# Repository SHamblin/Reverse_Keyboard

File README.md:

# Reverse_Keyboard
This is a diy mechanical keyboard with the numberpad on the left.

The primay goal of this project is to design a cherry mx compatable keyboard with the numberpad on the left.
Seconday goals include integrating a encoder for volume control a designing a stylish case
Stretch goals include intetgrating a fingerprint reader and a USB hub.

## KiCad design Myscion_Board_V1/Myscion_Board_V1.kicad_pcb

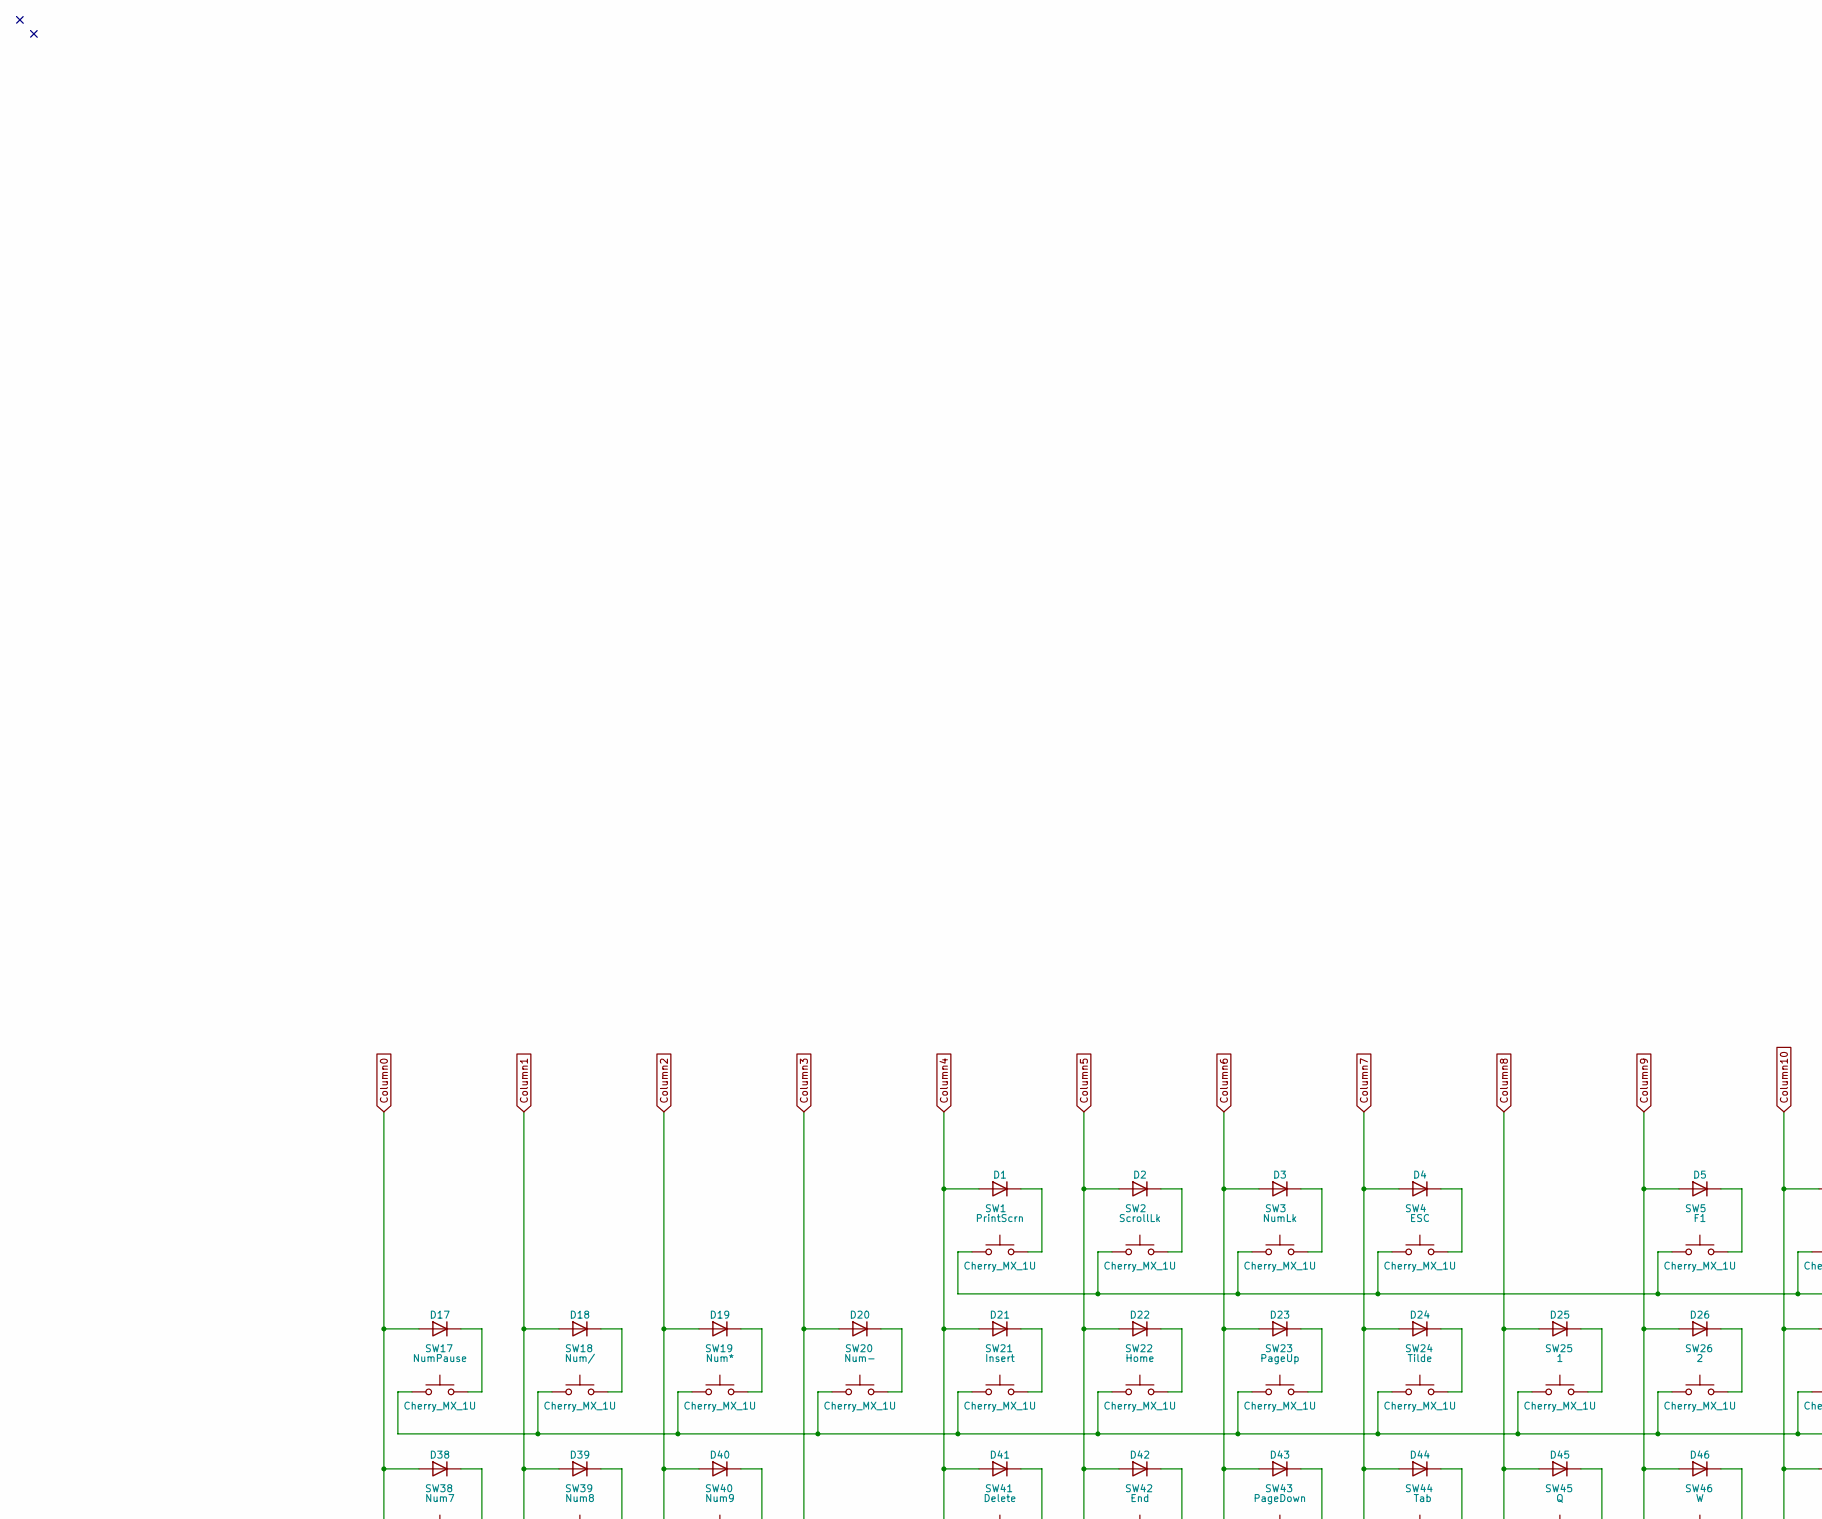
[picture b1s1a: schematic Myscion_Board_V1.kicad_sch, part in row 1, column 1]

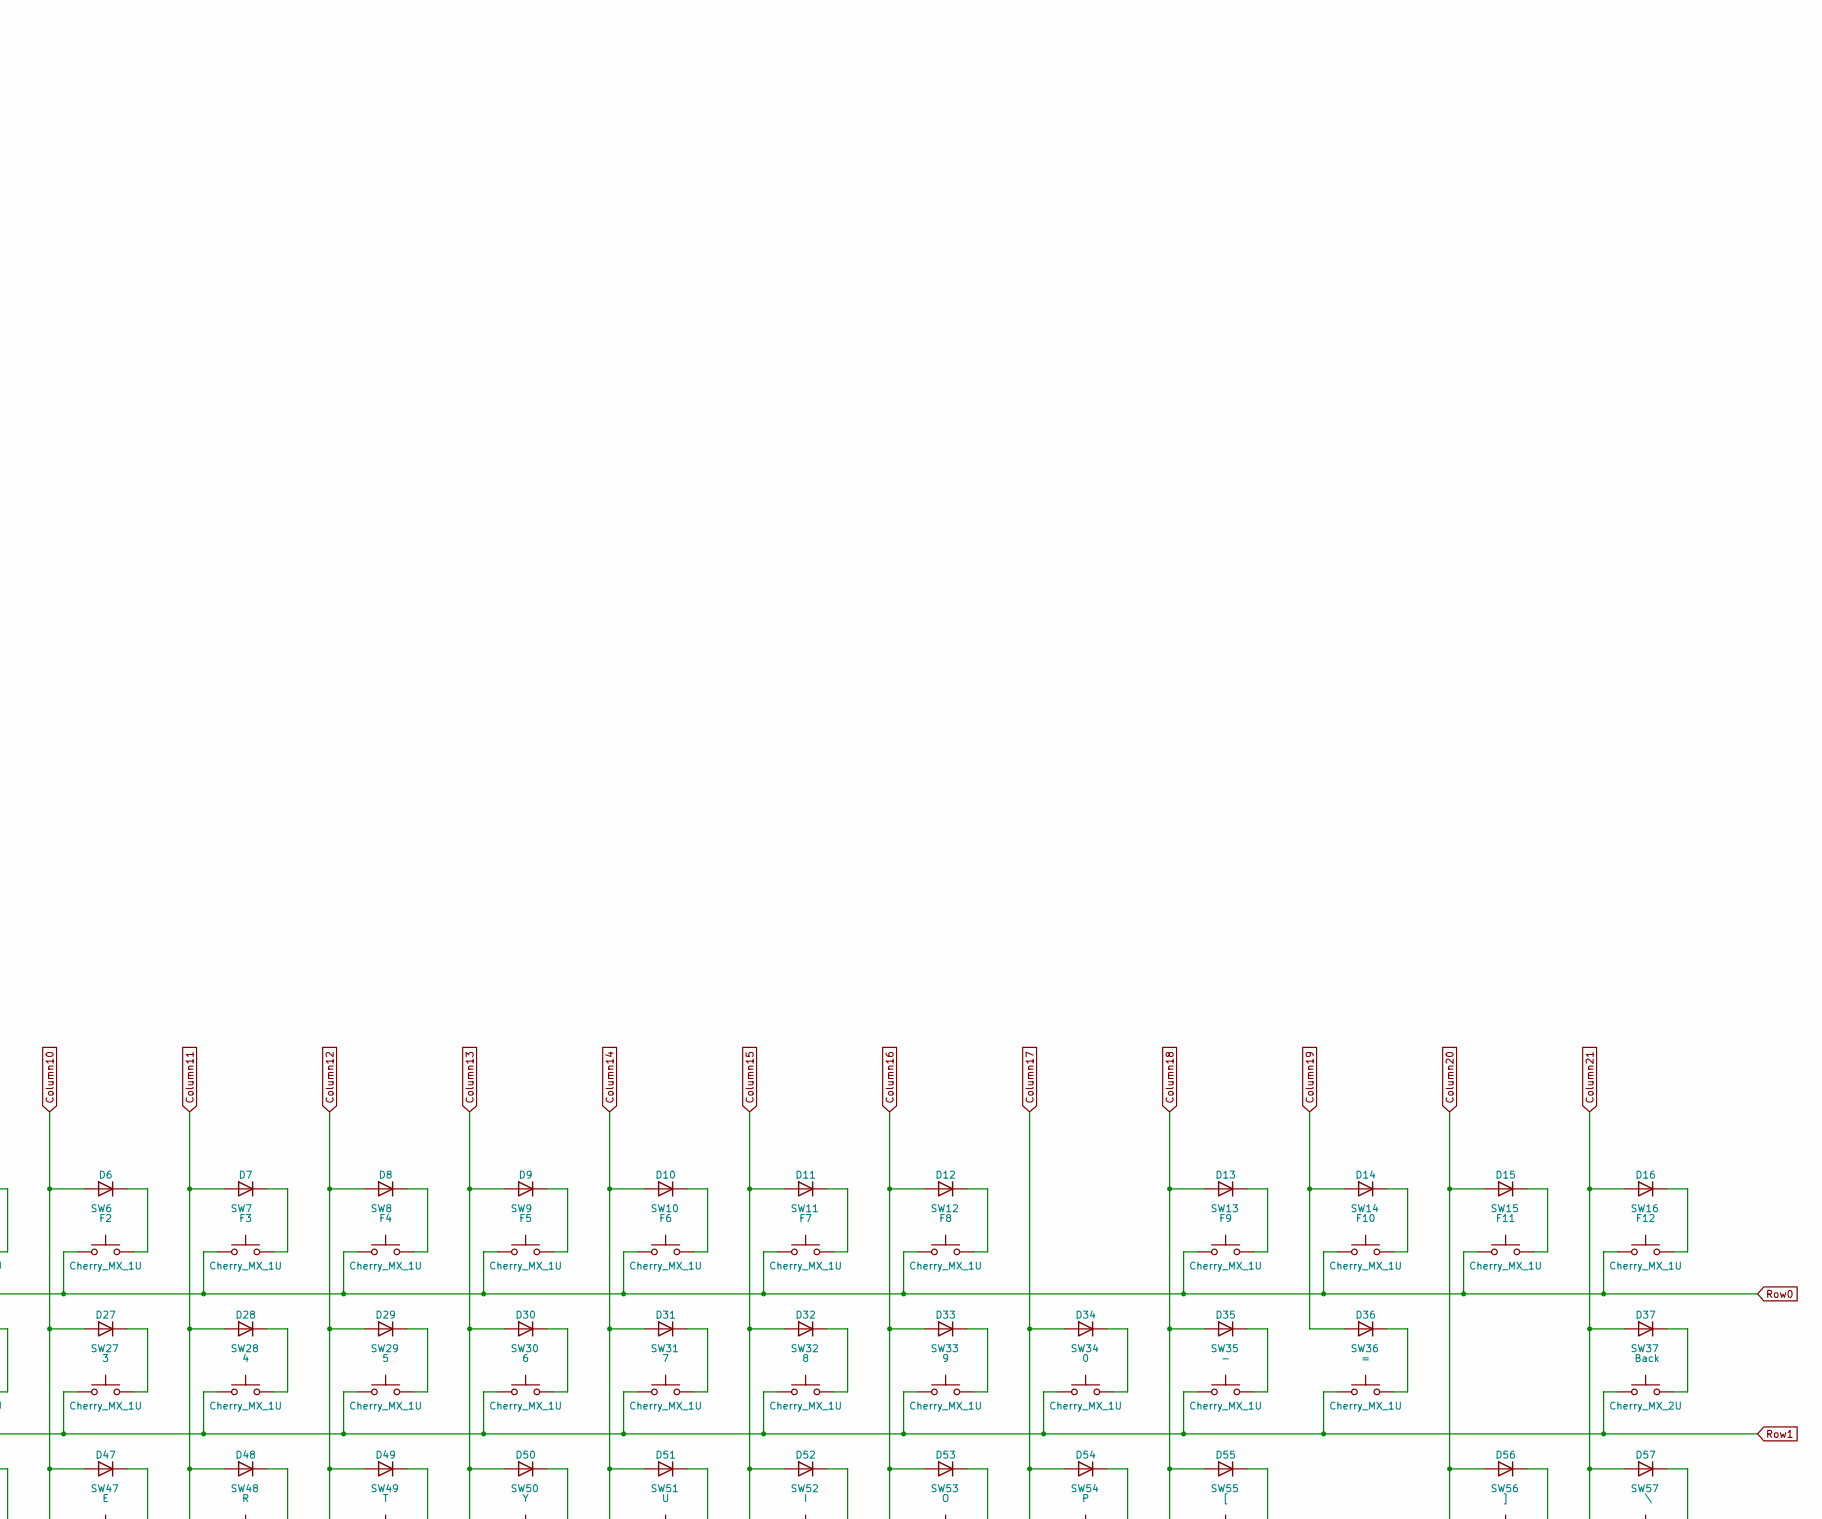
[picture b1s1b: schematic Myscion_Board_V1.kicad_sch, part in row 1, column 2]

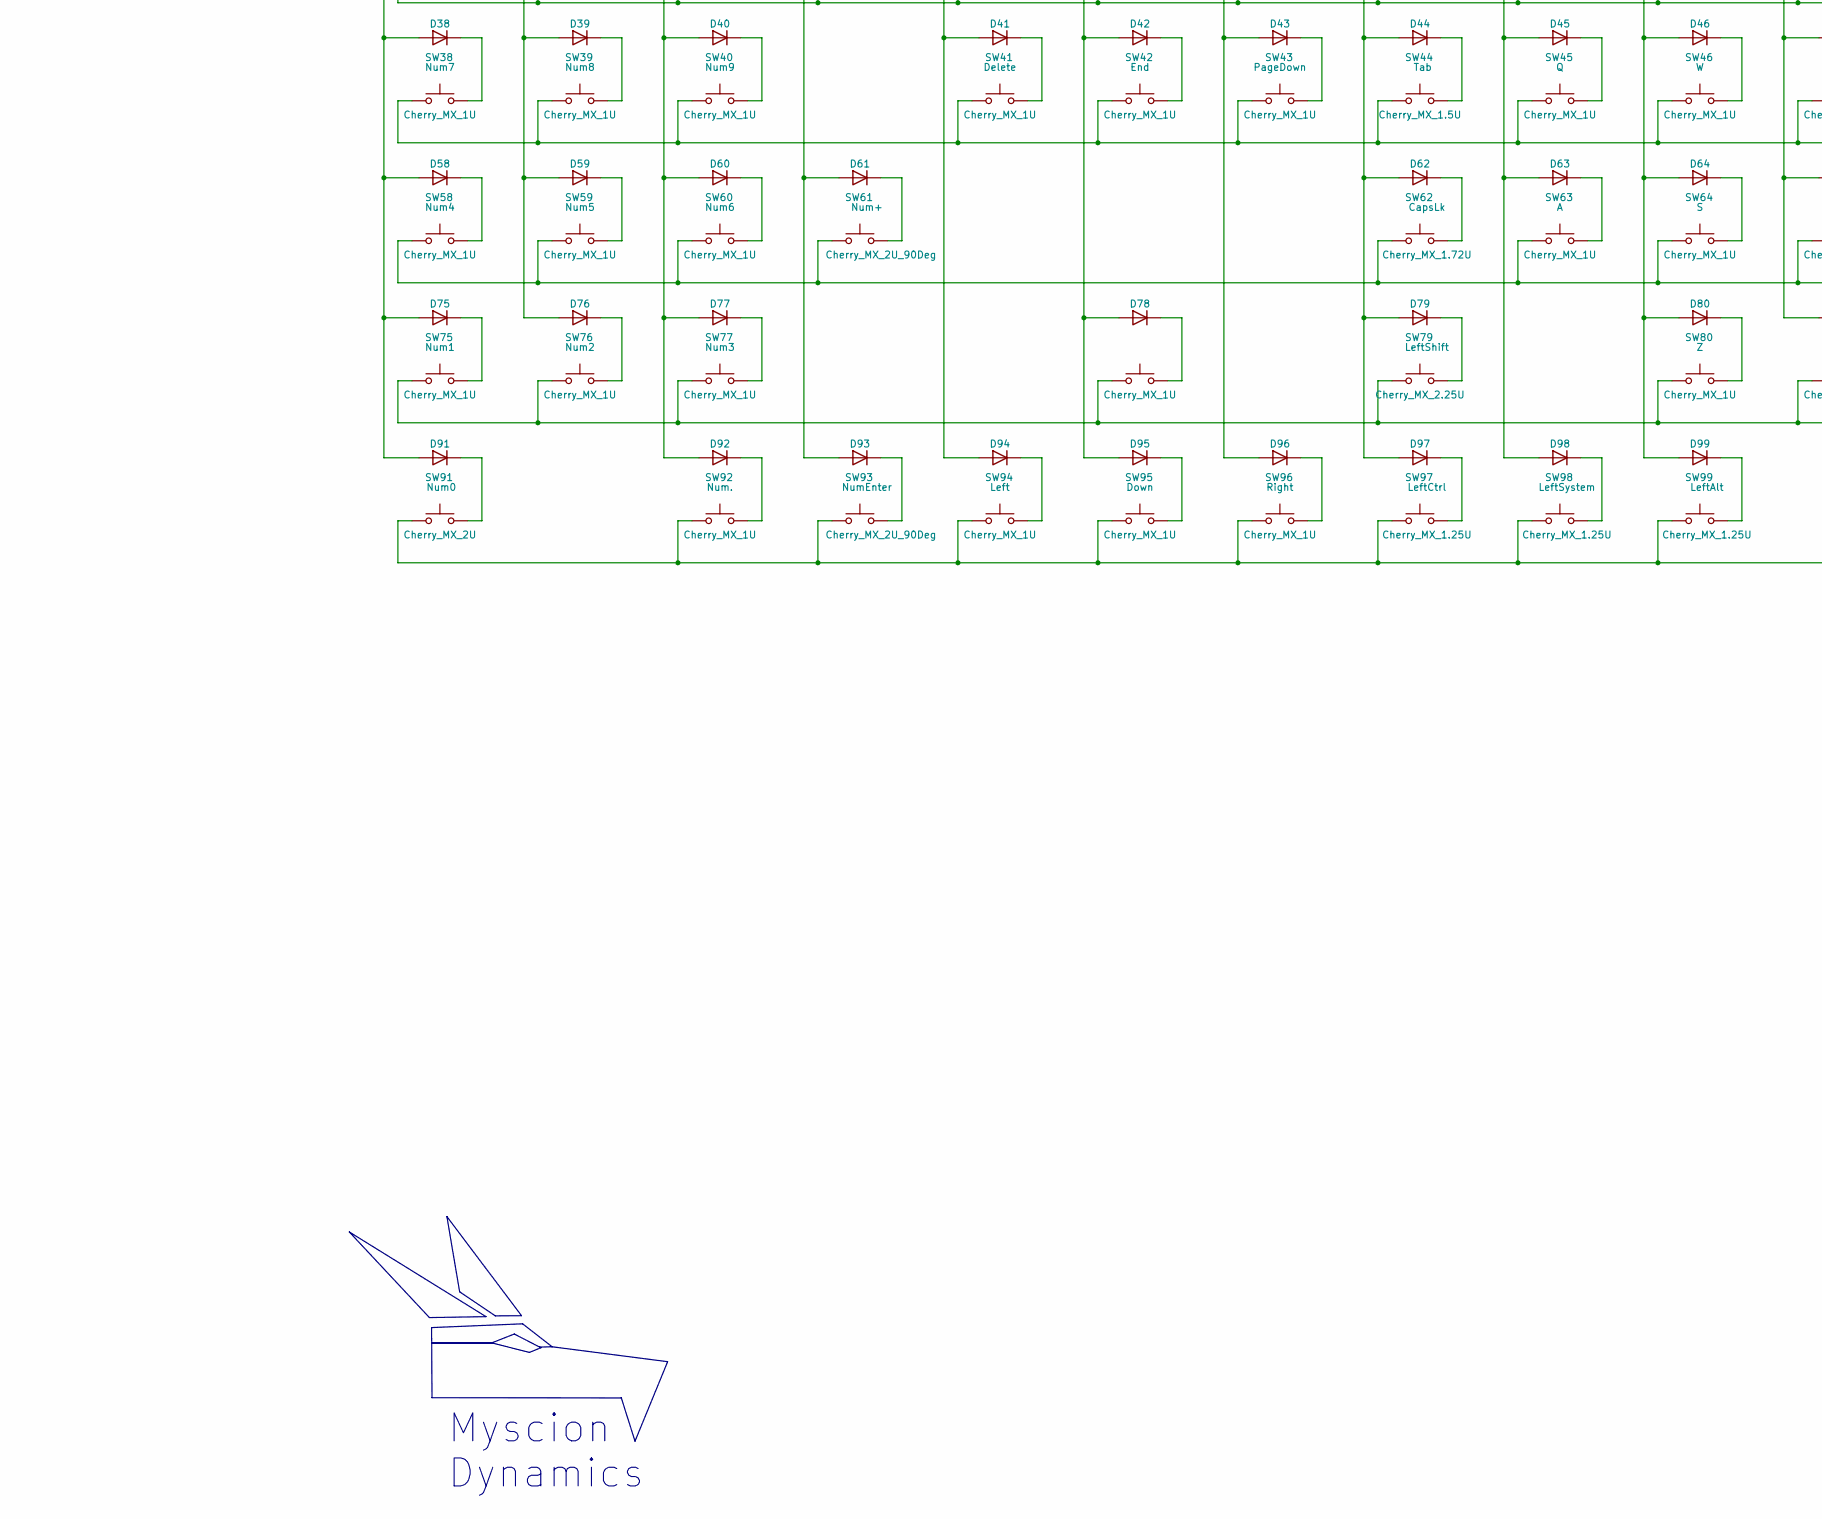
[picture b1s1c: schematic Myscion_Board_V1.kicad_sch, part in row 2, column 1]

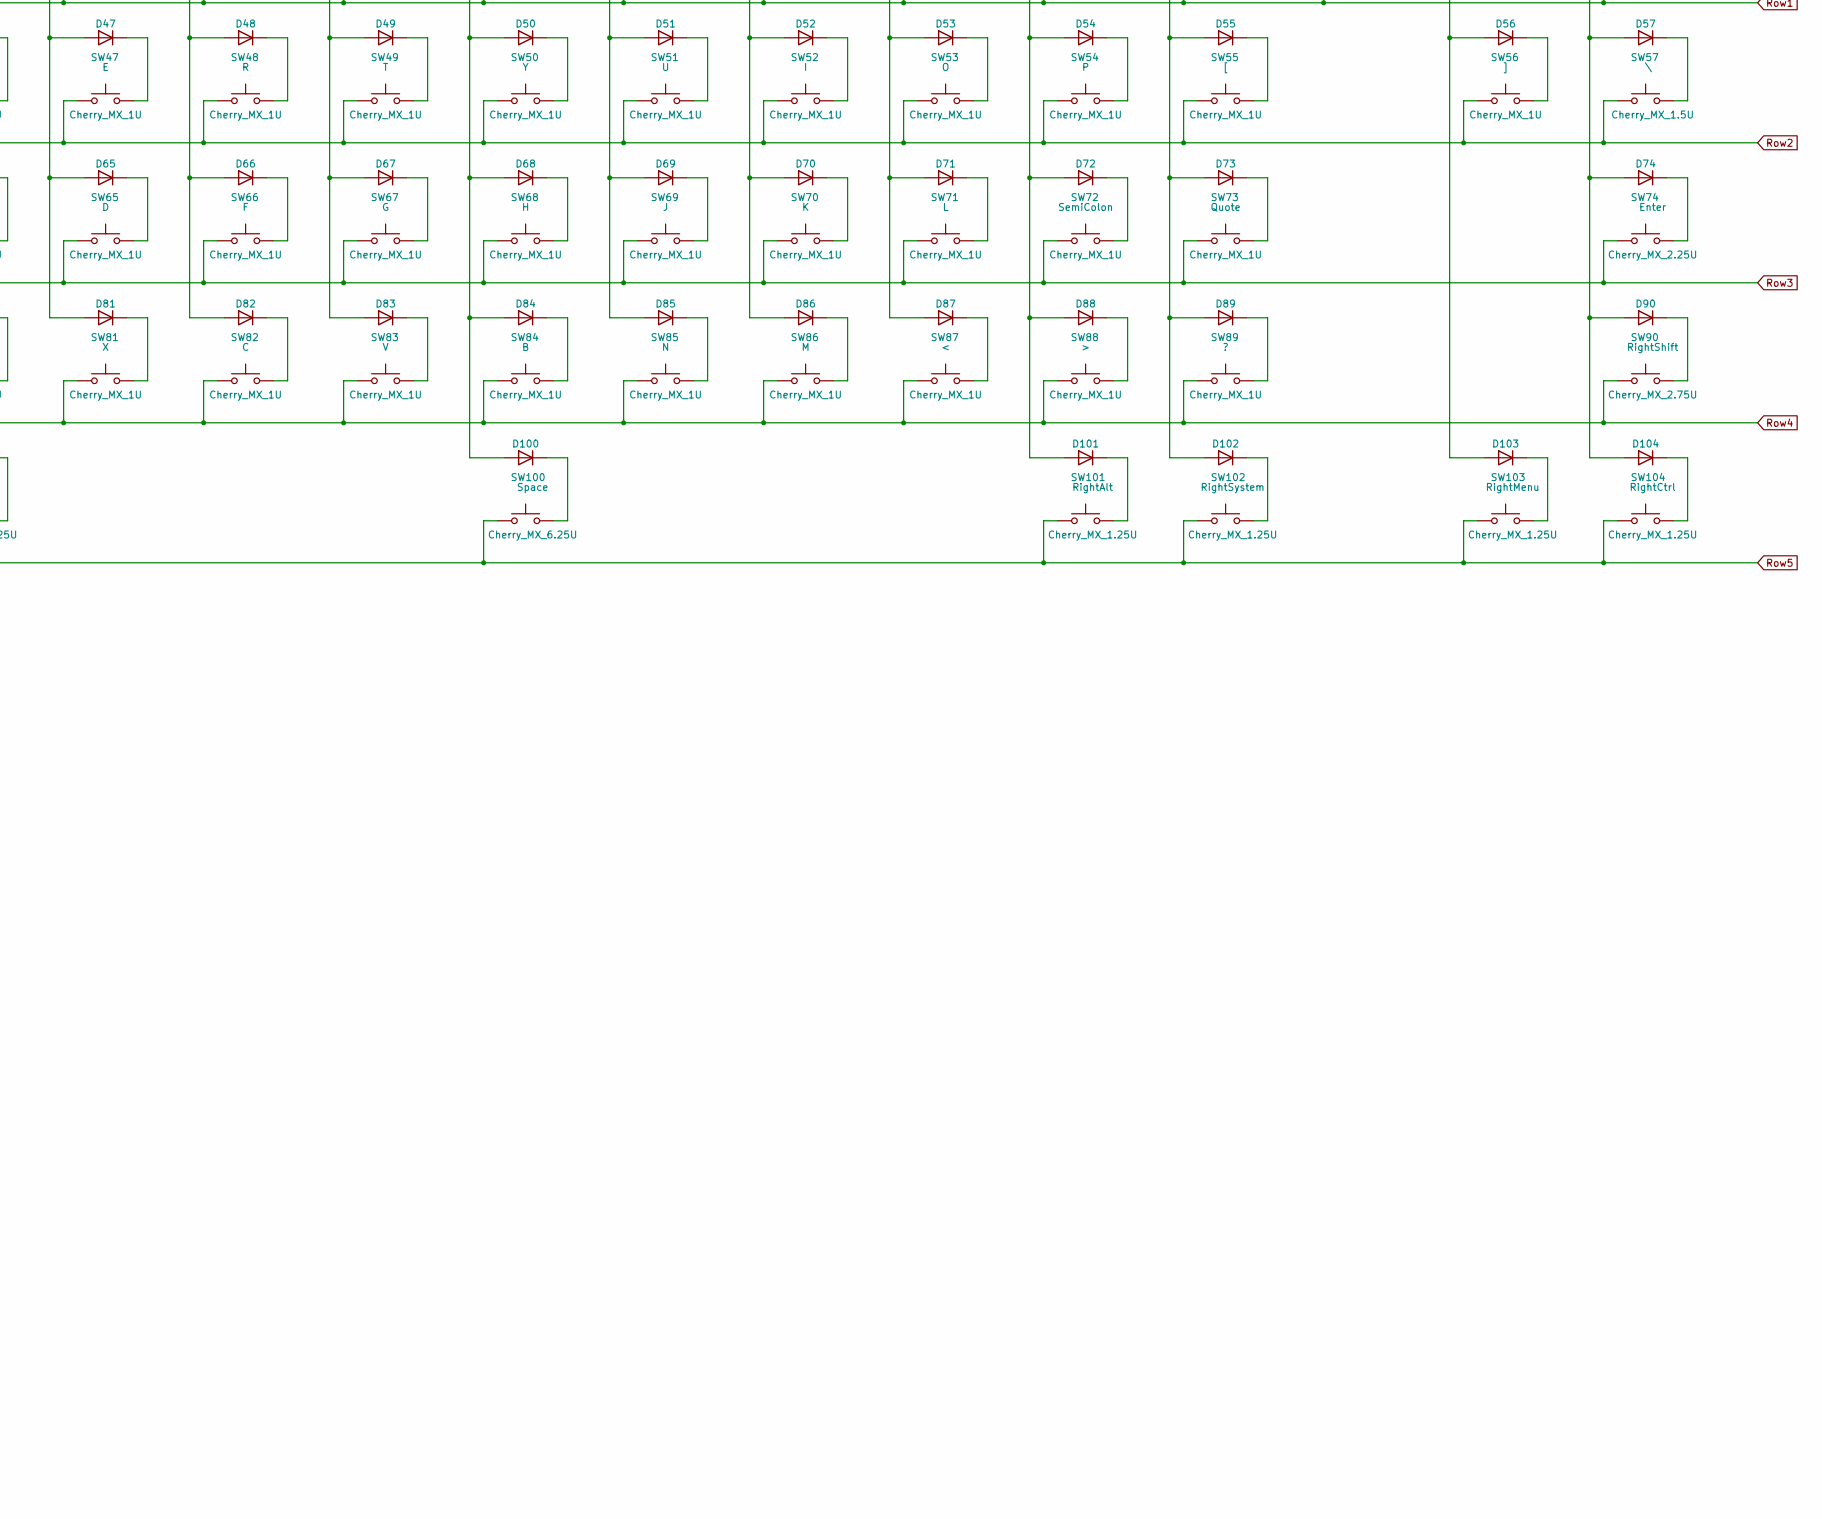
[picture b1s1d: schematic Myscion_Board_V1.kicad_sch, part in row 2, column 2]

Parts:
D1, D2, D3, D4, D5, D6, D7, D8, D9, D10, D11, D12, D13, D14, D15, D16, D17, D18, D19, D20, D21, D22, D23, D24, D25, D26, D27, D28, D29, D30, D31, D32, D33, D34, D35, D36, D37, D38, D39, D40, D41, D42, D43, D44, D45, D46, D47, D48, D49, D50, D51, D52, D53, D54, D55, D56, D57, D58, D59, D60, D61, D62, D63, D64, D65, D66, D67, D68, D69, D70, D71, D72, D73, D74, D75, D76, D77, D78, D79, D80, D81, D82, D83, D84, D85, D86, D87, D88, D89, D90, D91, D92, D93, D94, D95, D96, D97, D98, D99, D100, D101, D102, D103, D104: 75V; D_SOD-123; MPN 1N4148W
SW1: PrintScrn; SW_Cherry_MX_PCB_1.00u; MPN Unkown
SW2: ScrollLk; SW_Cherry_MX_PCB_1.00u; MPN Unkown
SW3: NumLk; SW_Cherry_MX_PCB_1.00u; MPN Unkown
SW4: ESC; SW_Cherry_MX_PCB_1.00u; MPN Unkown
SW5: F1; SW_Cherry_MX_PCB_1.00u; MPN Unkown
SW6: F2; SW_Cherry_MX_PCB_1.00u; MPN Unkown
SW7: F3; SW_Cherry_MX_PCB_1.00u; MPN Unkown
SW8: F4; SW_Cherry_MX_PCB_1.00u; MPN Unkown
SW9: F5; SW_Cherry_MX_PCB_1.00u; MPN Unkown
SW10: F6; SW_Cherry_MX_PCB_1.00u; MPN Unkown
SW11: F7; SW_Cherry_MX_PCB_1.00u; MPN Unkown
SW12: F8; SW_Cherry_MX_PCB_1.00u; MPN Unkown
SW13: F9; SW_Cherry_MX_PCB_1.00u; MPN Unkown
SW14: F10; SW_Cherry_MX_PCB_1.00u; MPN Unkown
SW15: F11; SW_Cherry_MX_PCB_1.00u; MPN Unkown
SW16: F12; SW_Cherry_MX_PCB_1.00u; MPN Unkown
SW17: NumPause; SW_Cherry_MX_PCB_1.00u; MPN Unkown
SW18: Num/; SW_Cherry_MX_PCB_1.00u; MPN Unkown
SW19: Num*; SW_Cherry_MX_PCB_1.00u; MPN Unkown
SW20: Num-; SW_Cherry_MX_PCB_1.00u; MPN Unkown
SW21: Insert; SW_Cherry_MX_PCB_1.00u; MPN Unkown
SW22: Home; SW_Cherry_MX_PCB_1.00u; MPN Unkown
SW23: PageUp; SW_Cherry_MX_PCB_1.00u; MPN Unkown
SW24: Tilde; SW_Cherry_MX_PCB_1.00u; MPN Unkown
SW25: 1; SW_Cherry_MX_PCB_1.00u; MPN Unkown
SW26: 2; SW_Cherry_MX_PCB_1.00u; MPN Unkown
SW27: 3; SW_Cherry_MX_PCB_1.00u; MPN Unkown
SW28: 4; SW_Cherry_MX_PCB_1.00u; MPN Unkown
SW29: 5; SW_Cherry_MX_PCB_1.00u; MPN Unkown
SW30: 6; SW_Cherry_MX_PCB_1.00u; MPN Unkown
SW31: 7; SW_Cherry_MX_PCB_1.00u; MPN Unkown
SW32: 8; SW_Cherry_MX_PCB_1.00u; MPN Unkown
SW33: 9; SW_Cherry_MX_PCB_1.00u; MPN Unkown
SW34: 0; SW_Cherry_MX_PCB_1.00u; MPN Unkown
SW35: -; SW_Cherry_MX_PCB_1.00u; MPN Unkown
SW36: =; SW_Cherry_MX_PCB_1.00u; MPN Unkown
SW37: Back; SW_Cherry_MX_PCB_2.00u; MPN Unkown
SW38: Num7; SW_Cherry_MX_PCB_1.00u; MPN Unkown
SW39: Num8; SW_Cherry_MX_PCB_1.00u; MPN Unkown
SW40: Num9; SW_Cherry_MX_PCB_1.00u; MPN Unkown
SW41: Delete; SW_Cherry_MX_PCB_1.00u; MPN Unkown
SW42: End; SW_Cherry_MX_PCB_1.00u; MPN Unkown
SW43: PageDown; SW_Cherry_MX_PCB_1.00u; MPN Unkown
SW44: Tab; SW_Cherry_MX_PCB_1.50u; MPN Unkown
SW45: Q; SW_Cherry_MX_PCB_1.00u; MPN Unkown
SW46: W; SW_Cherry_MX_PCB_1.00u; MPN Unkown
SW47: E; SW_Cherry_MX_PCB_1.00u; MPN Unkown
SW48: R; SW_Cherry_MX_PCB_1.00u; MPN Unkown
SW49: T; SW_Cherry_MX_PCB_1.00u; MPN Unkown
SW50: Y; SW_Cherry_MX_PCB_1.00u; MPN Unkown
SW51: U; SW_Cherry_MX_PCB_1.00u; MPN Unkown
SW52: I; SW_Cherry_MX_PCB_1.00u; MPN Unkown
SW53: O; SW_Cherry_MX_PCB_1.00u; MPN Unkown
SW54: P; SW_Cherry_MX_PCB_1.00u; MPN Unkown
SW55: [; SW_Cherry_MX_PCB_1.00u; MPN Unkown
SW56: ]; SW_Cherry_MX_PCB_1.00u; MPN Unkown
SW57: \; SW_Cherry_MX_PCB_1.50u; MPN Unkown
SW58: Num4; SW_Cherry_MX_PCB_1.00u; MPN Unkown
SW59: Num5; SW_Cherry_MX_PCB_1.00u; MPN Unkown
SW60: Num6; SW_Cherry_MX_PCB_1.00u; MPN Unkown
SW61: Num+; SW_Cherry_MX_PCB_2.00u_90deg; MPN Unkown
SW62: CapsLk; SW_Cherry_MX_PCB_1.75u; MPN Unkown
SW63: A; SW_Cherry_MX_PCB_1.00u; MPN Unkown
SW64: S; SW_Cherry_MX_PCB_1.00u; MPN Unkown
SW65: D; SW_Cherry_MX_PCB_1.00u; MPN Unkown
SW66: F; SW_Cherry_MX_PCB_1.00u; MPN Unkown
SW67: G; SW_Cherry_MX_PCB_1.00u; MPN Unkown
SW68: H; SW_Cherry_MX_PCB_1.00u; MPN Unkown
SW69: J; SW_Cherry_MX_PCB_1.00u; MPN Unkown
SW70: K; SW_Cherry_MX_PCB_1.00u; MPN Unkown
SW71: L; SW_Cherry_MX_PCB_1.00u; MPN Unkown
SW72: SemiColon; SW_Cherry_MX_PCB_1.00u; MPN Unkown
SW73: Quote; SW_Cherry_MX_PCB_1.00u; MPN Unkown
SW74: Enter; SW_Cherry_MX_PCB_2.25u; MPN Unkown
SW75: Num1; SW_Cherry_MX_PCB_1.00u; MPN Unkown
SW76: Num2; SW_Cherry_MX_PCB_1.00u; MPN Unkown
SW77: Num3; SW_Cherry_MX_PCB_1.00u; MPN Unkown
SW78: Up; SW_Cherry_MX_PCB_1.00u; MPN Unkown
SW79: LeftShift; SW_Cherry_MX_PCB_2.25u; MPN Unkown
SW80: Z; SW_Cherry_MX_PCB_1.00u; MPN Unkown
SW81: X; SW_Cherry_MX_PCB_1.00u; MPN Unkown
SW82: C; SW_Cherry_MX_PCB_1.00u; MPN Unkown
SW83: V; SW_Cherry_MX_PCB_1.00u; MPN Unkown
SW84: B; SW_Cherry_MX_PCB_1.00u; MPN Unkown
SW85: N; SW_Cherry_MX_PCB_1.00u; MPN Unkown
SW86: M; SW_Cherry_MX_PCB_1.00u; MPN Unkown
SW87: <; SW_Cherry_MX_PCB_1.00u; MPN Unkown
SW88: >; SW_Cherry_MX_PCB_1.00u; MPN Unkown
SW89: ?; SW_Cherry_MX_PCB_1.00u; MPN Unkown
SW90: RightShift; SW_Cherry_MX_PCB_2.75u; MPN Unkown
SW91: Num0; SW_Cherry_MX_PCB_2.00u; MPN Unkown
SW92: Num.; SW_Cherry_MX_PCB_1.00u; MPN Unkown
SW93: NumEnter; SW_Cherry_MX_PCB_2.00u_90deg; MPN Unkown
SW94: Left; SW_Cherry_MX_PCB_1.00u; MPN Unkown
SW95: Down; SW_Cherry_MX_PCB_1.00u; MPN Unkown
SW96: Right; SW_Cherry_MX_PCB_1.00u; MPN Unkown
SW97: LeftCtrl; SW_Cherry_MX_PCB_1.25u; MPN Unkown
SW98: LeftSystem; SW_Cherry_MX_PCB_1.25u; MPN Unkown
SW99: LeftAlt; SW_Cherry_MX_PCB_1.25u; MPN Unkown
SW100: Space; SW_Cherry_MX_PCB_6.25u; MPN Unkown
SW101: RightAlt; SW_Cherry_MX_PCB_1.25u; MPN Unkown
SW102: RightSystem; SW_Cherry_MX_PCB_1.25u; MPN Unkown
SW103: RightMenu; SW_Cherry_MX_PCB_1.25u; MPN Unkown
SW104: RightCtrl; SW_Cherry_MX_PCB_1.25u; MPN Unkown

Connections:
Column0: D17.2 (A), D38.2 (A), D58.2 (A), D75.2 (A), D91.2 (A)
Column1: D18.2 (A), D39.2 (A), D59.2 (A), D76.2 (A)
Column2: D19.2 (A), D40.2 (A), D60.2 (A), D77.2 (A), D92.2 (A)
Column3: D20.2 (A), D61.2 (A), D93.2 (A)
Column4: D1.2 (A), D21.2 (A), D41.2 (A), D94.2 (A)
Column5: D2.2 (A), D22.2 (A), D42.2 (A), D78.2 (A), D95.2 (A)
Column6: D3.2 (A), D23.2 (A), D43.2 (A), D96.2 (A)
Column7: D4.2 (A), D24.2 (A), D44.2 (A), D62.2 (A), D79.2 (A), D97.2 (A)
Column8: D25.2 (A), D45.2 (A), D63.2 (A), D98.2 (A)
Column9: D5.2 (A), D26.2 (A), D46.2 (A), D64.2 (A), D80.2 (A), D99.2 (A)
Column10: D6.2 (A), D27.2 (A), D47.2 (A), D65.2 (A), D81.2 (A)
Column11: D7.2 (A), D28.2 (A), D48.2 (A), D66.2 (A), D82.2 (A)
Column12: D8.2 (A), D29.2 (A), D49.2 (A), D67.2 (A), D83.2 (A)
Column13: D9.2 (A), D30.2 (A), D50.2 (A), D68.2 (A), D84.2 (A), D100.2 (A)
Column14: D10.2 (A), D31.2 (A), D51.2 (A), D69.2 (A), D85.2 (A)
Column15: D11.2 (A), D32.2 (A), D52.2 (A), D70.2 (A), D86.2 (A)
Column16: D12.2 (A), D33.2 (A), D53.2 (A), D71.2 (A), D87.2 (A)
Column17: D34.2 (A), D54.2 (A), D72.2 (A), D88.2 (A), D101.2 (A)
Column18: D13.2 (A), D35.2 (A), D55.2 (A), D73.2 (A), D89.2 (A), D102.2 (A)
Column19: D14.2 (A), D36.2 (A)
Column20: D15.2 (A), D56.2 (A), D103.2 (A)
Column21: D16.2 (A), D37.2 (A), D57.2 (A), D74.2 (A), D90.2 (A), D104.2 (A)
unnamed: D1.1 (K), SW1.2
unnamed: D2.1 (K), SW2.2
unnamed: D3.1 (K), SW3.2
unnamed: D4.1 (K), SW4.2
unnamed: D5.1 (K), SW5.2
unnamed: D6.1 (K), SW6.2
unnamed: D7.1 (K), SW7.2
unnamed: D8.1 (K), SW8.2
unnamed: D9.1 (K), SW9.2
unnamed: D10.1 (K), SW10.2
unnamed: D11.1 (K), SW11.2
unnamed: D12.1 (K), SW12.2
unnamed: D13.1 (K), SW13.2
unnamed: D14.1 (K), SW14.2
unnamed: D15.1 (K), SW15.2
unnamed: D16.1 (K), SW16.2
unnamed: D17.1 (K), SW17.2
unnamed: D18.1 (K), SW18.2
unnamed: D19.1 (K), SW19.2
unnamed: D20.1 (K), SW20.2
unnamed: D21.1 (K), SW21.2
unnamed: D22.1 (K), SW22.2
unnamed: D23.1 (K), SW23.2
unnamed: D24.1 (K), SW24.2
unnamed: D25.1 (K), SW25.2
unnamed: D26.1 (K), SW26.2
unnamed: D27.1 (K), SW27.2
unnamed: D28.1 (K), SW28.2
unnamed: D29.1 (K), SW29.2
unnamed: D30.1 (K), SW30.2
unnamed: D31.1 (K), SW31.2
unnamed: D32.1 (K), SW32.2
unnamed: D33.1 (K), SW33.2
unnamed: D34.1 (K), SW34.2
unnamed: D35.1 (K), SW35.2
unnamed: D36.1 (K), SW36.2
unnamed: D37.1 (K), SW37.2
unnamed: D38.1 (K), SW38.2
unnamed: D39.1 (K), SW39.2
unnamed: D40.1 (K), SW40.2
unnamed: D41.1 (K), SW41.2
unnamed: D42.1 (K), SW42.2
unnamed: D43.1 (K), SW43.2
unnamed: D44.1 (K), SW44.2
unnamed: D45.1 (K), SW45.2
unnamed: D46.1 (K), SW46.2
unnamed: D47.1 (K), SW47.2
unnamed: D48.1 (K), SW48.2
unnamed: D49.1 (K), SW49.2
unnamed: D50.1 (K), SW50.2
unnamed: D51.1 (K), SW51.2
unnamed: D52.1 (K), SW52.2
unnamed: D53.1 (K), SW53.2
unnamed: D54.1 (K), SW54.2
unnamed: D55.1 (K), SW55.2
unnamed: D56.1 (K), SW56.2
unnamed: D57.1 (K), SW57.2
unnamed: D58.1 (K), SW58.2
unnamed: D59.1 (K), SW59.2
unnamed: D60.1 (K), SW60.2
unnamed: D61.1 (K), SW61.2
unnamed: D62.1 (K), SW62.2
unnamed: D63.1 (K), SW63.2
unnamed: D64.1 (K), SW64.2
unnamed: D65.1 (K), SW65.2
unnamed: D66.1 (K), SW66.2
unnamed: D67.1 (K), SW67.2
unnamed: D68.1 (K), SW68.2
unnamed: D69.1 (K), SW69.2
unnamed: D70.1 (K), SW70.2
unnamed: D71.1 (K), SW71.2
unnamed: D72.1 (K), SW72.2
unnamed: D73.1 (K), SW73.2
unnamed: D74.1 (K), SW74.2
unnamed: D75.1 (K), SW75.2
unnamed: D76.1 (K), SW76.2
unnamed: D77.1 (K), SW77.2
unnamed: D78.1 (K), SW78.2
unnamed: D79.1 (K), SW79.2
unnamed: D80.1 (K), SW80.2
unnamed: D81.1 (K), SW81.2
unnamed: D82.1 (K), SW82.2
unnamed: D83.1 (K), SW83.2
unnamed: D84.1 (K), SW84.2
unnamed: D85.1 (K), SW85.2
unnamed: D86.1 (K), SW86.2
unnamed: D87.1 (K), SW87.2
unnamed: D88.1 (K), SW88.2
unnamed: D89.1 (K), SW89.2
unnamed: D90.1 (K), SW90.2
unnamed: D91.1 (K), SW91.2
unnamed: D92.1 (K), SW92.2
unnamed: D93.1 (K), SW93.2
unnamed: D94.1 (K), SW94.2
unnamed: D95.1 (K), SW95.2
unnamed: D96.1 (K), SW96.2
unnamed: D97.1 (K), SW97.2
unnamed: D98.1 (K), SW98.2
unnamed: D99.1 (K), SW99.2
unnamed: D100.1 (K), SW100.2
unnamed: D101.1 (K), SW101.2
unnamed: D102.1 (K), SW102.2
unnamed: D103.1 (K), SW103.2
unnamed: D104.1 (K), SW104.2
Row0: SW1.1, SW2.1, SW3.1, SW4.1, SW5.1, SW6.1, SW7.1, SW8.1, SW9.1, SW10.1, SW11.1, SW12.1, SW13.1, SW14.1, SW15.1, SW16.1
Row1: SW17.1, SW18.1, SW19.1, SW20.1, SW21.1, SW22.1, SW23.1, SW24.1, SW25.1, SW26.1, SW27.1, SW28.1, SW29.1, SW30.1, SW31.1, SW32.1, SW33.1, SW34.1, SW35.1, SW36.1, SW37.1
Row2: SW38.1, SW39.1, SW40.1, SW41.1, SW42.1, SW43.1, SW44.1, SW45.1, SW46.1, SW47.1, SW48.1, SW49.1, SW50.1, SW51.1, SW52.1, SW53.1, SW54.1, SW55.1, SW56.1, SW57.1
Row3: SW58.1, SW59.1, SW60.1, SW61.1, SW62.1, SW63.1, SW64.1, SW65.1, SW66.1, SW67.1, SW68.1, SW69.1, SW70.1, SW71.1, SW72.1, SW73.1, SW74.1
Row4: SW75.1, SW76.1, SW77.1, SW78.1, SW79.1, SW80.1, SW81.1, SW82.1, SW83.1, SW84.1, SW85.1, SW86.1, SW87.1, SW88.1, SW89.1, SW90.1
Row5: SW91.1, SW92.1, SW93.1, SW94.1, SW95.1, SW96.1, SW97.1, SW98.1, SW99.1, SW100.1, SW101.1, SW102.1, SW103.1, SW104.1

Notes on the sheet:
Myscion Dynamics

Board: 2 copper layers, 208 parts (0 on the bottom side), 132 nets, no tracks yet.

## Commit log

2024-04-14 Initial commit with rough schematic layout
2024-04-14 Keyboard Matrix complete
2024-04-14 Moved diode to other side to aid in layout
2024-04-14 Key foot prints placed and locked down for the main keyboard
